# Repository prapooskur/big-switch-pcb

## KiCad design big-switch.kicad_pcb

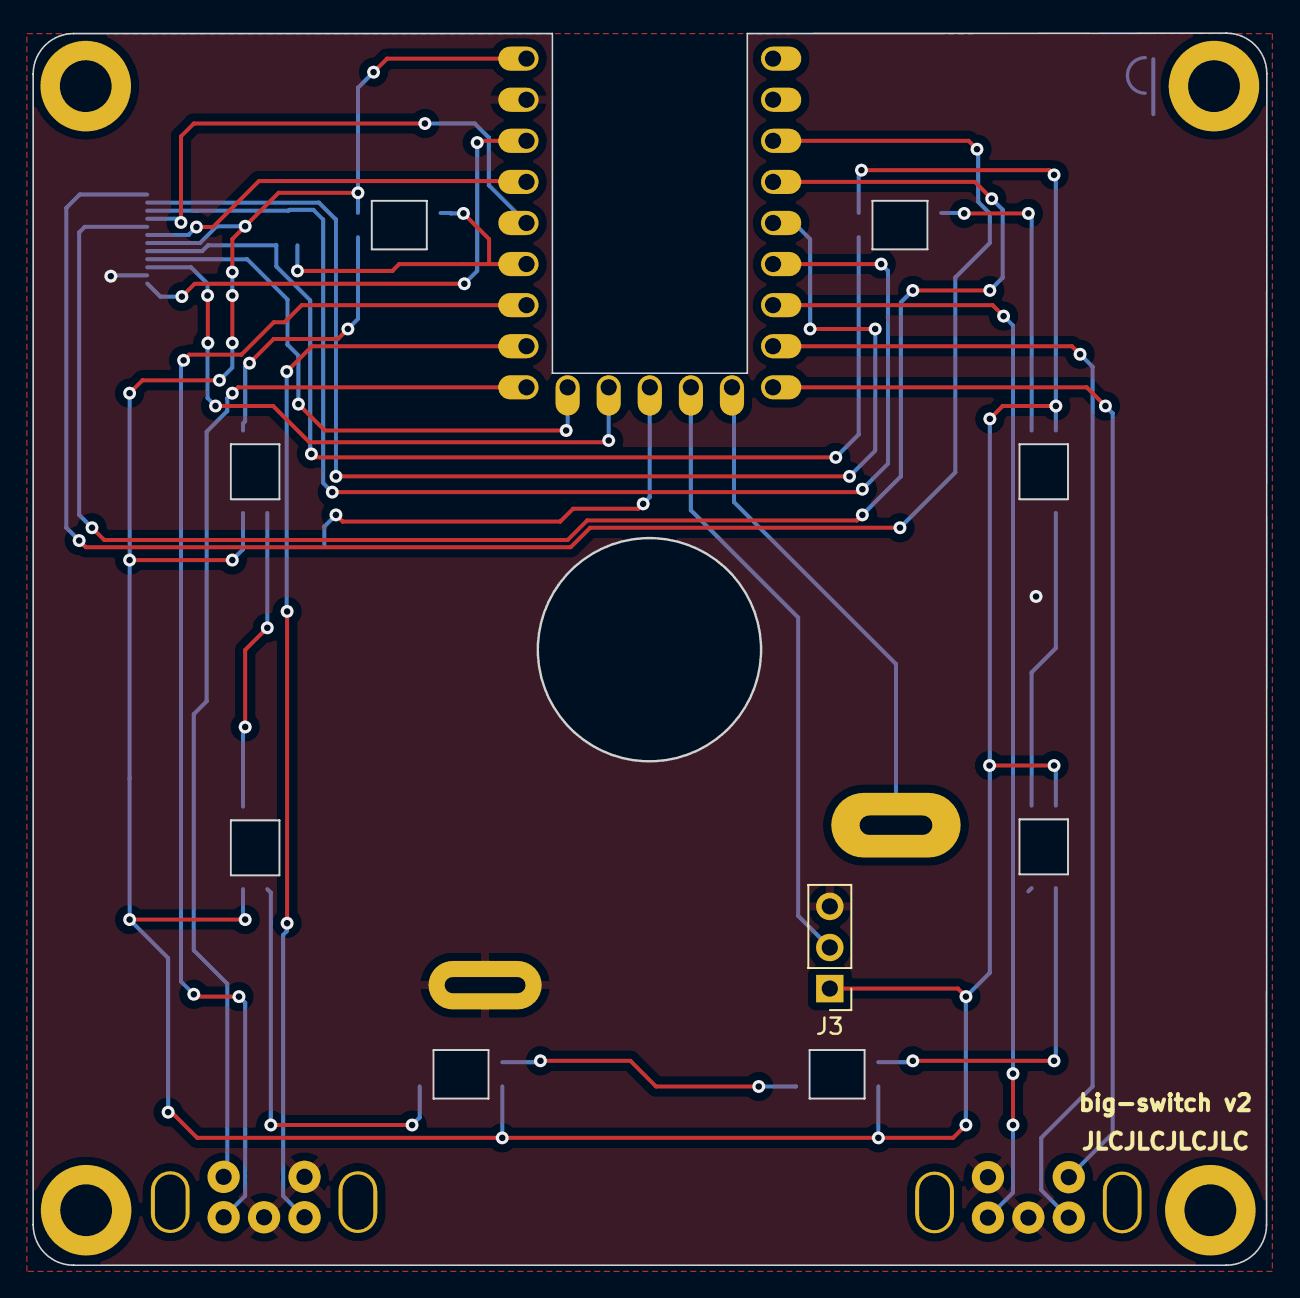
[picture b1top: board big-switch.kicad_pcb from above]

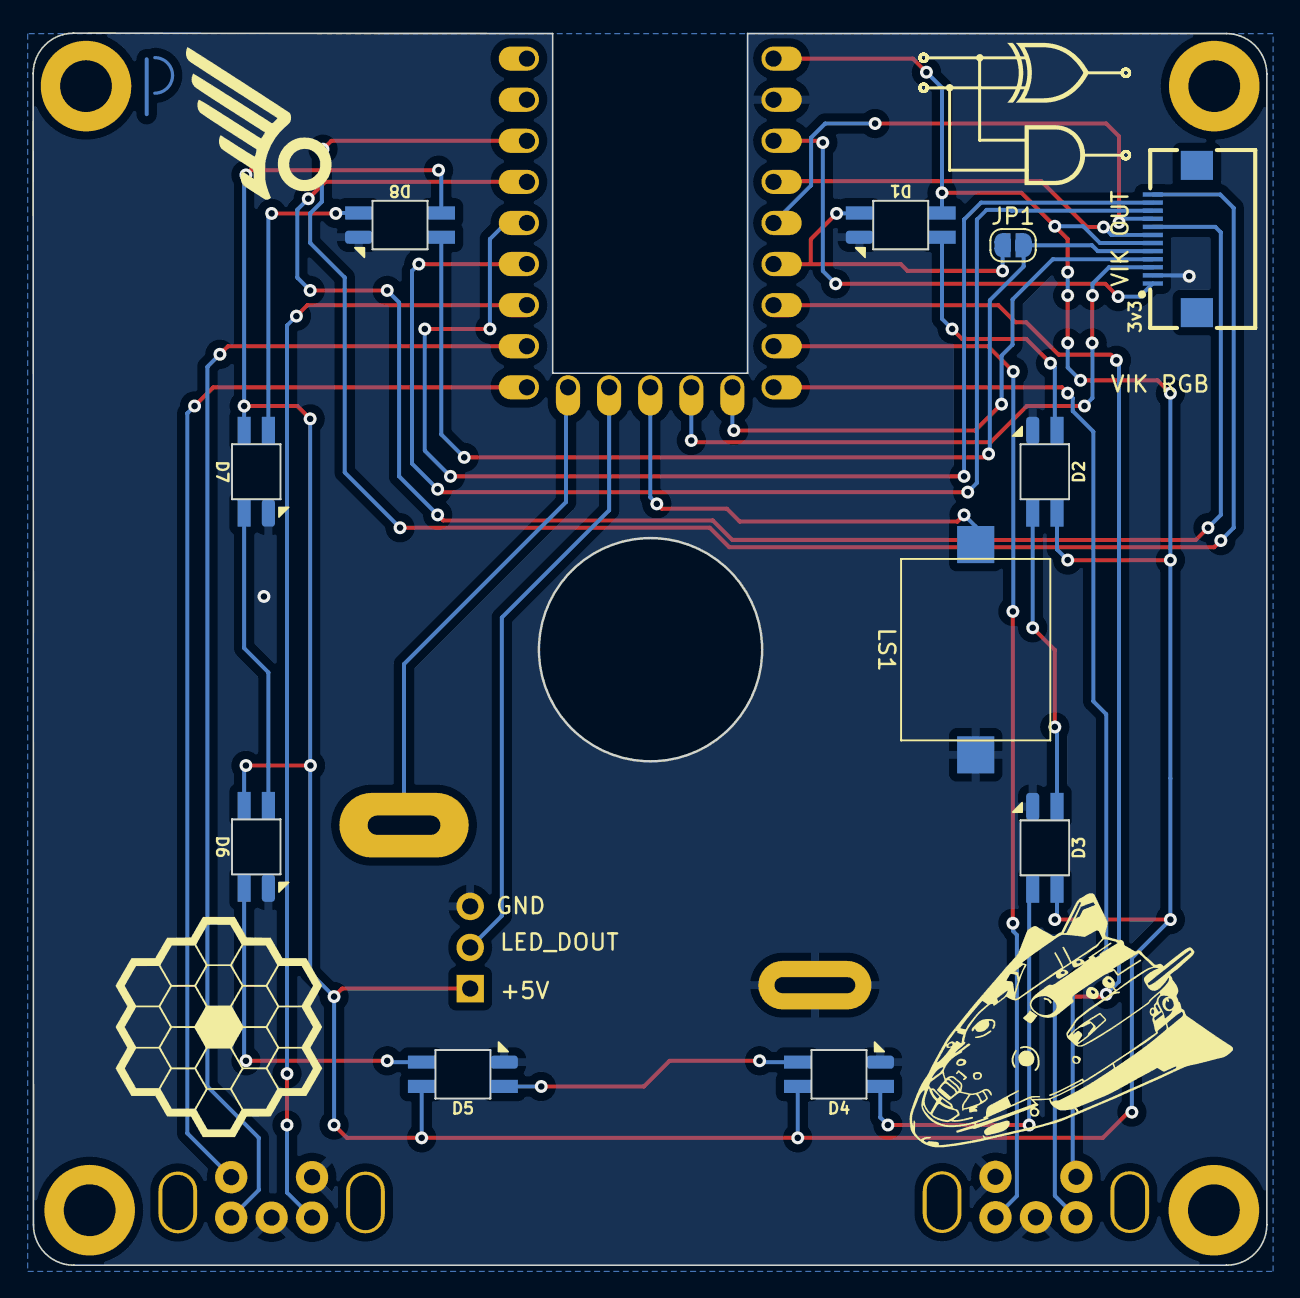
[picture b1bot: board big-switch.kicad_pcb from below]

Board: 2 copper layers, 76.2 x 76.1 mm, 16 parts (11 on the bottom side), 29 nets.

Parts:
D1, D2, D3, D4, D5, D6, D7, D8: SK6812MINI-E; SK6812-MINI-E
J2: vik-keyboard-connector-horizontal
J3: Conn_01x03_Socket; PinHeader_1x03_P2.54mm_Vertical
JP1: Jumper_2_Open; SolderJumper-2_P1.3mm_Open_RoundedPad1.0x1.5mm
LS1: Speaker; AST1109MLTRQ
SW1: SW_Push; NovelKeys_Kailh_Big_Series_Switch
SW2, SW3: RotaryEncoder_Switch; RotaryEncoder_EC11B-Horizontal-Dual
U2: rp2040-zero; rp2040-zero-tht

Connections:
+3V3: J2.1 (3V3), U2.21 (3V3)
+5V: D1.1 (VDD), D2.1 (VDD), D3.1 (VDD), D4.1 (VDD), D5.1 (VDD), D6.1 (VDD), D7.1 (VDD), D8.1 (VDD), J2.6 (5V), J3.1, U2.23 (5V)
AUDIO: LS1.2, U2.12 (11)
ENC1_A: SW2.A, U2.17 (26)
ENC1_B: SW2.B, U2.16 (15)
ENC1_SW: SW2.S1, U2.15 (14)
ENC2_A: SW3.A, U2.7 (6)
ENC2_B: SW3.B, U2.8 (7)
ENC2_SW: SW3.S2, U2.9 (8)
GND: D1.3 (VSS), D2.3 (VSS), D3.3 (VSS), D4.3 (VSS), D5.3 (VSS), D6.3 (VSS), D7.3 (VSS), D8.3 (VSS), J2.2 (GND), J3.3, LS1.1, SW1.2, SW2.C, SW2.S2, SW3.C, SW3.S1, U2.22 (GND)
GPIO_X1: J2.7 (GPIO_AD1), U2.20 (29)
GPIO_X2: J2.9 (GPIO_AD2), U2.19 (28)
LED_RING: J3.2, U2.11 (10)
MISO: J2.11 (MISO), U2.5 (4)
MOSI: J2.8 (MOSI), U2.4 (3)
unnamed: D1.2 (DOUT), D2.4 (DIN)
unnamed: D2.2 (DOUT), D3.4 (DIN)
unnamed: D3.2 (DOUT), D4.4 (DIN)
unnamed: D4.2 (DOUT), D5.4 (DIN)
unnamed: D5.2 (DOUT), D6.4 (DIN)
unnamed: D6.2 (DOUT), D7.4 (DIN)
unnamed: D7.2 (DOUT), D8.4 (DIN)
RGB_DIN: D1.4 (DIN), JP1.1 (A), U2.18 (27)
SCL: J2.4 (SCL), U2.14 (13)
SCLK: J2.12 (SCLK), U2.3 (2)
SDA: J2.3 (SDA), U2.13 (12)
SW_1: SW1.1, U2.10 (9)
VIK_CS: J2.10 (SPI_CS), U2.6 (5)
VIK_RGB: D8.2 (DOUT), J2.5 (RGB_LED_OUT), JP1.2 (B)

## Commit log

2023-11-14 init update
2023-11-14 routing ocmplete
2023-11-15 flipped mcu side, rerouted
2023-11-15 added screenshots
2023-11-15 rounded corners
2023-11-20 added LED
2024-01-04 Create LICENSE
2024-02-20 updted to support rp2040-zero
